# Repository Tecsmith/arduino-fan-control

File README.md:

# Qwiic Fan Control Module

- This is the **EAGLE** *PCB* design project
- For the **Arduino** *code* library please see [Tecsmith](https://github.com/Tecsmith)/[Tecsmith_AMC6821](https://github.com/Tecsmith/Tecsmith_AMC6821)

AMC6821 based Fan Control Module with Qwiic connectors for integration into 3.3V MCU projects.

| &#8505; | URL |
|--------:|-----|
| Project website | [tecsmith.github.io/arduino-fan-control](https://tecsmith.github.io/arduino-fan-control/) |
| Quick link | [`c1k.it/amc6`](http://c1k.it/amc6) |
| Github EAGLE-CAD Source | https://github.com/Tecsmith/arduino-fan-control/tree/master/EAGLE |
| Github PlatformIO Source | https://github.com/Tecsmith/arduino-fan-control/tree/master/PlatformIO |

## About

Thermal control is often arbitrarily implemented in electronics projects – adoption of fans for heat management is often done without consideration for power consumption or acoustic noise.

Leveraging the Texas Instruments AMC6821 chip, this module adds an intelligent temperature monitor and pulse-width modulation (PWM) fan controller to a fan. It is designed for noise-sensitive or power-sensitive applications that require active system cooling. Using a PWM signal, this device simultaneously drives a fan, monitors remote sensor diode temperatures, and measures/controls the fan speed so that it operates with minimal acoustic noise at the lowest possible speed.

This project is an Open Source Hardware (OSH) project and is based on [SparkFun's Qwiic](https://www.sparkfun.com/qwiic) I<sup>2</sup>C connectors and can be integrated into many 3.3V based MCU's.

## AMC6821
### Intelligent temperature monitor and pulse-width modulation fan controller

The AMC6821 is an intelligent temperature monitor and pulse-width modulation (PWM) fan controller. It is designed for noise-sensitive or power-sensitive applications that require active system cooling. Using a low-frequency or a high-frequency PWM signal, this device can simultaneously drive a fan, monitor remote sensor diode temperatures, and measure and control the fan speed so that it operates with minimal acoustic noise at the lowest possible speed.

The AMC6821 has four fan control modes: *Auto Temperature-Fan* mode, *Software-RPM* mode, *Software-DCY* mode, and *Maximum fast-speed calculated control* mode.  Each mode controls the fan speed by changing the duty cycle of a PWM output.

- <u>**Auto Temperature-Fan**</u> mode is an intelligent, closed-loop control that optimizes fan speed according to user-defined parameters. This mode allows the AMC6821 to run as a stand-alone device without CPU intervention; the fan can continue to be controlled (based on temperature measurements) even if the CPU or system locks up.

- <u>**Software-RPM**</u> mode is a second closed-loop control. In this mode, the AMC6821 adjusts the PWM output to maintain a consistent fan speed at a user-specified target value; that is, the device functions as a fan speed regulator. Software-RPM mode can also be used to allow the AMC6821 to operate as a stand-alone device.

- <u>**Software-DCY**</u> mode is the third mode and is open-loop. In Software-DCY mode, the PWM duty cycle is set directly by the value written to the device.

- <u>**Maximum fast-speed calculated control**</u> mode.

The AMC6821 also has a programmable `SMBALERT` output to indicate error conditions and a dedicated `FAN-FAULT` output to indicate fan failure. The `THERM` pin is a fail-safe output for over-temperature conditions that can be used to throttle a CPU clock. Additionally, the `OVR` pin indicates the over-temperature limit as well. All of the alarm thresholds are set through the device registers. The AMC6821 is available in a QSOP-16 package.

## Project Features

- Designed to be an inline series add-on for existing fan implementations.
- Can be powered from 12V and/or 5V power sources. _(Dependant on Fan required operational voltage.)_
- Support most fan types, 5V~ and 12V
  * 4-wire _(Tachometer + PWM)_
  * 3-wire _(Tachometer Sensor)~_
  * 3-wire _(Locked Rotor Sensor)~_
  * 2-wire~
- Can be run as standalone module.
- Can be chained for up to 9 fans, depending on I<sup>2</sup>C addresses set at A0 and A1 pins.
- Both Qwiic and generic I<sup>2</sup>C headers for communication with 3.3V based MCU boards.

> *~ = with add-on MOSFET*

----------
<p align="center" style="color:#069">&#9733;</p>

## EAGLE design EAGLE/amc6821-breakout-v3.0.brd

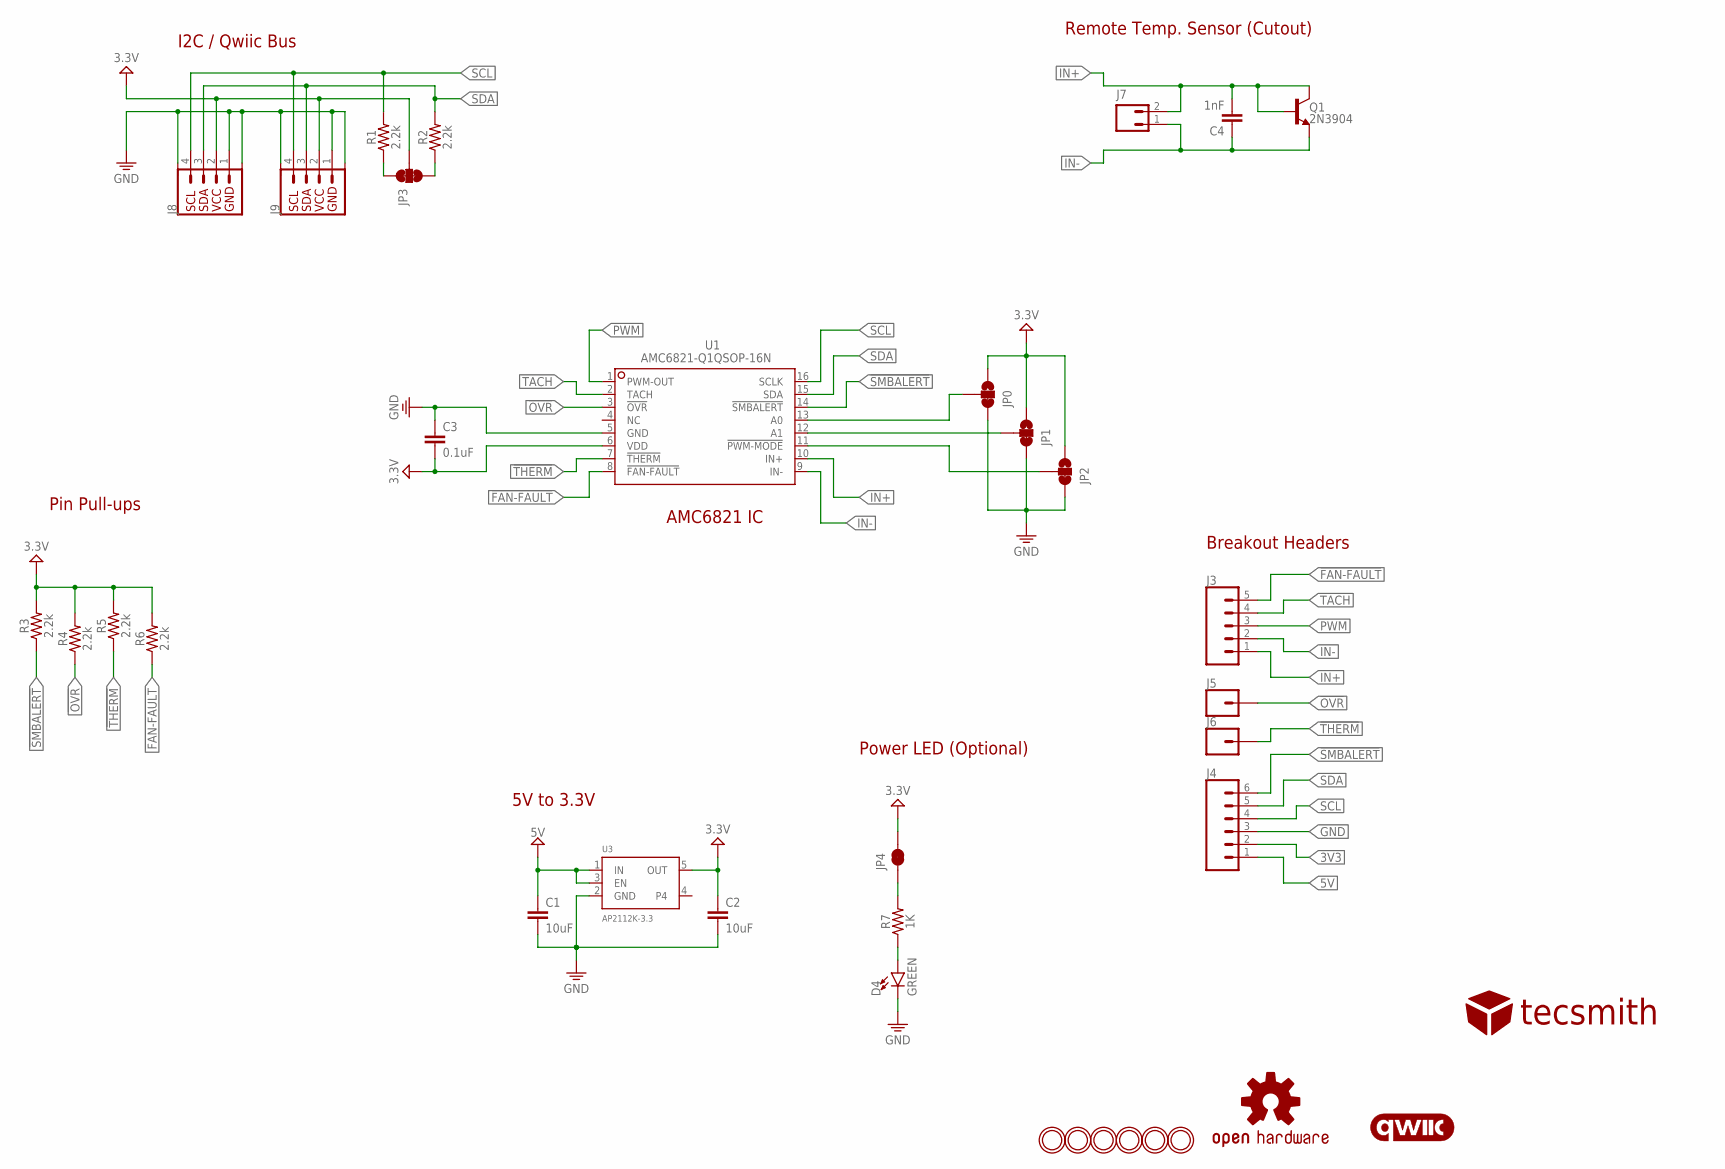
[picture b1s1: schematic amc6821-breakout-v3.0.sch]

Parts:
C1, C2: 10uF; 0603
C3: 0.1uF; 0603
C4: 1nF; 0603
D4: GREEN; LED-0603
J3: CONN_05; 1X05
J4: CONN_06SILK_FEMALE_PTH; 1X06
J5, J6: CONN_01; 1X01
J7: CONN_02; 1X02-LONG
J8, J9: QWIIC_RIGHT_ANGLE; JST04_1MM_RA
JP0, JP1, JP2: JUMPER-SMT_3_1-NC_TRACE_SILK; SMT-JUMPER_3_1-NC_TRACE_SILK
JP3: JUMPER-SMT_3_2-NC_TRACE_SILK; SMT-JUMPER_3_2-NC_TRACE_SILK
JP4: JUMPER-SMT_2_NC_TRACE_SILK; SMT-JUMPER_2_NC_TRACE_SILK
LOGO1: OSHW-LOGOS; OSHW-LOGO-S
LOGO2: QWIIC_LOGO_6MM; QWIIC_6MM
Q1: 2N3904; SOT23-3
R1, R2, R3, R4, R5, R6: 2.2k; 0603
R7: 1K; 0805
U1: AMC6821-Q1QSOP-16N; QSOP-16N
U3: AP2112K-3.3; SOT23-5
U$1: TECSMITH-LOGO
U$4, U$5, U$7, U$8, U$9, U$10: MOUNTINGHOLE2.5; MOUNTINGHOLE_2.5_PLATED

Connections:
3V3: C2.1, C3.2, J4.2, J8.2, J9.2, JP0.1, JP1.1, JP2.1, JP3.2, JP4.2, R3.2, R4.2, R5.2, R6.2, U1.6 (VDD), U3.5 (OUT)
5V: C1.1, J4.1, U3.1 (IN), U3.3 (EN)
!FAN-FAULT: J3.5, R6.1, U1.8 (!FAN-FAULT)
!OVR: J5.1, R4.1, U1.3 (!OVR)
!SMBALERT: J4.6, R3.1, U1.14 (!SMBALERT)
!THERM: J6.1, R5.1, U1.7 (!THERM)
GND: C1.2, C2.2, C3.1, D4.C, J4.3, J8.1, J8.NC1, J8.NC2, J9.1, J9.NC1, J9.NC2, JP0.3, JP1.3, JP2.3, U1.5 (GND), U3.2 (GND)
IN+: C4.2, J3.1, J7.2, Q1.1 (B), Q1.3 (C), U1.10 (IN+)
IN-: C4.1, J3.2, J7.1, Q1.2 (E), U1.9 (IN-)
unnamed: JP0.2, U1.13 (A0)
unnamed: JP3.3, R2.1
unnamed: JP3.1, R1.1
unnamed: JP2.2, U1.11 (!PWM-MODE)
unnamed: JP1.2, U1.12 (A1)
unnamed: D4.A, R7.1
unnamed: JP4.1, R7.2
PWM: J3.3, U1.1 (PWM-OUT)
SCL: J4.4, J8.4, J9.4, R1.2, U1.16 (SCLK)
SDA: J4.5, J8.3, J9.3, R2.2, U1.15 (SDA)
TACH: J3.4, U1.2 (TACH)

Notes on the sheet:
I2C / Qwiic Bus
Breakout Headers
5V to 3.3V
AMC6821 IC
Remote Temp. Sensor (Cutout)
Pin Pull-ups
Power LED (Optional)

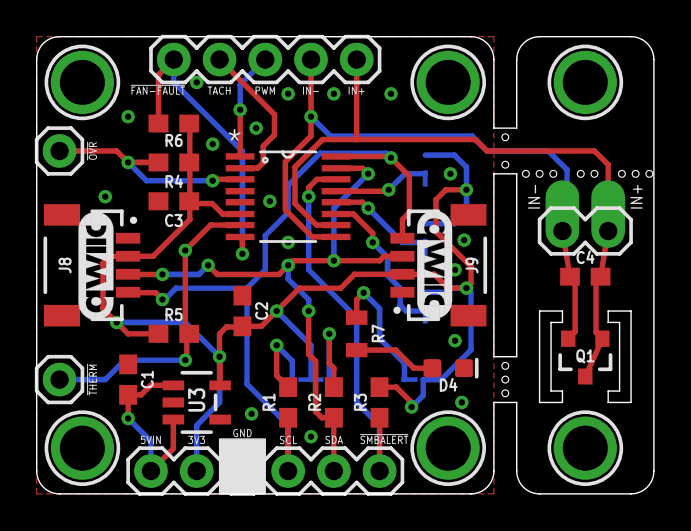
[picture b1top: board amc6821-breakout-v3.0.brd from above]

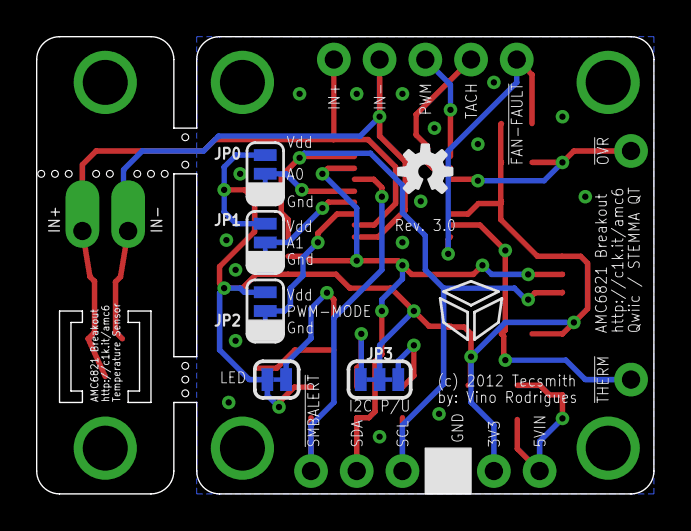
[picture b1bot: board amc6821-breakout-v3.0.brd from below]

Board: 2 copper layers, 34.3 x 25.4 mm, 37 parts (7 on the bottom side), 20 nets.

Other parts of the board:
LOGO3: QWIIC_LOGO_6MM; QWIIC_6MM

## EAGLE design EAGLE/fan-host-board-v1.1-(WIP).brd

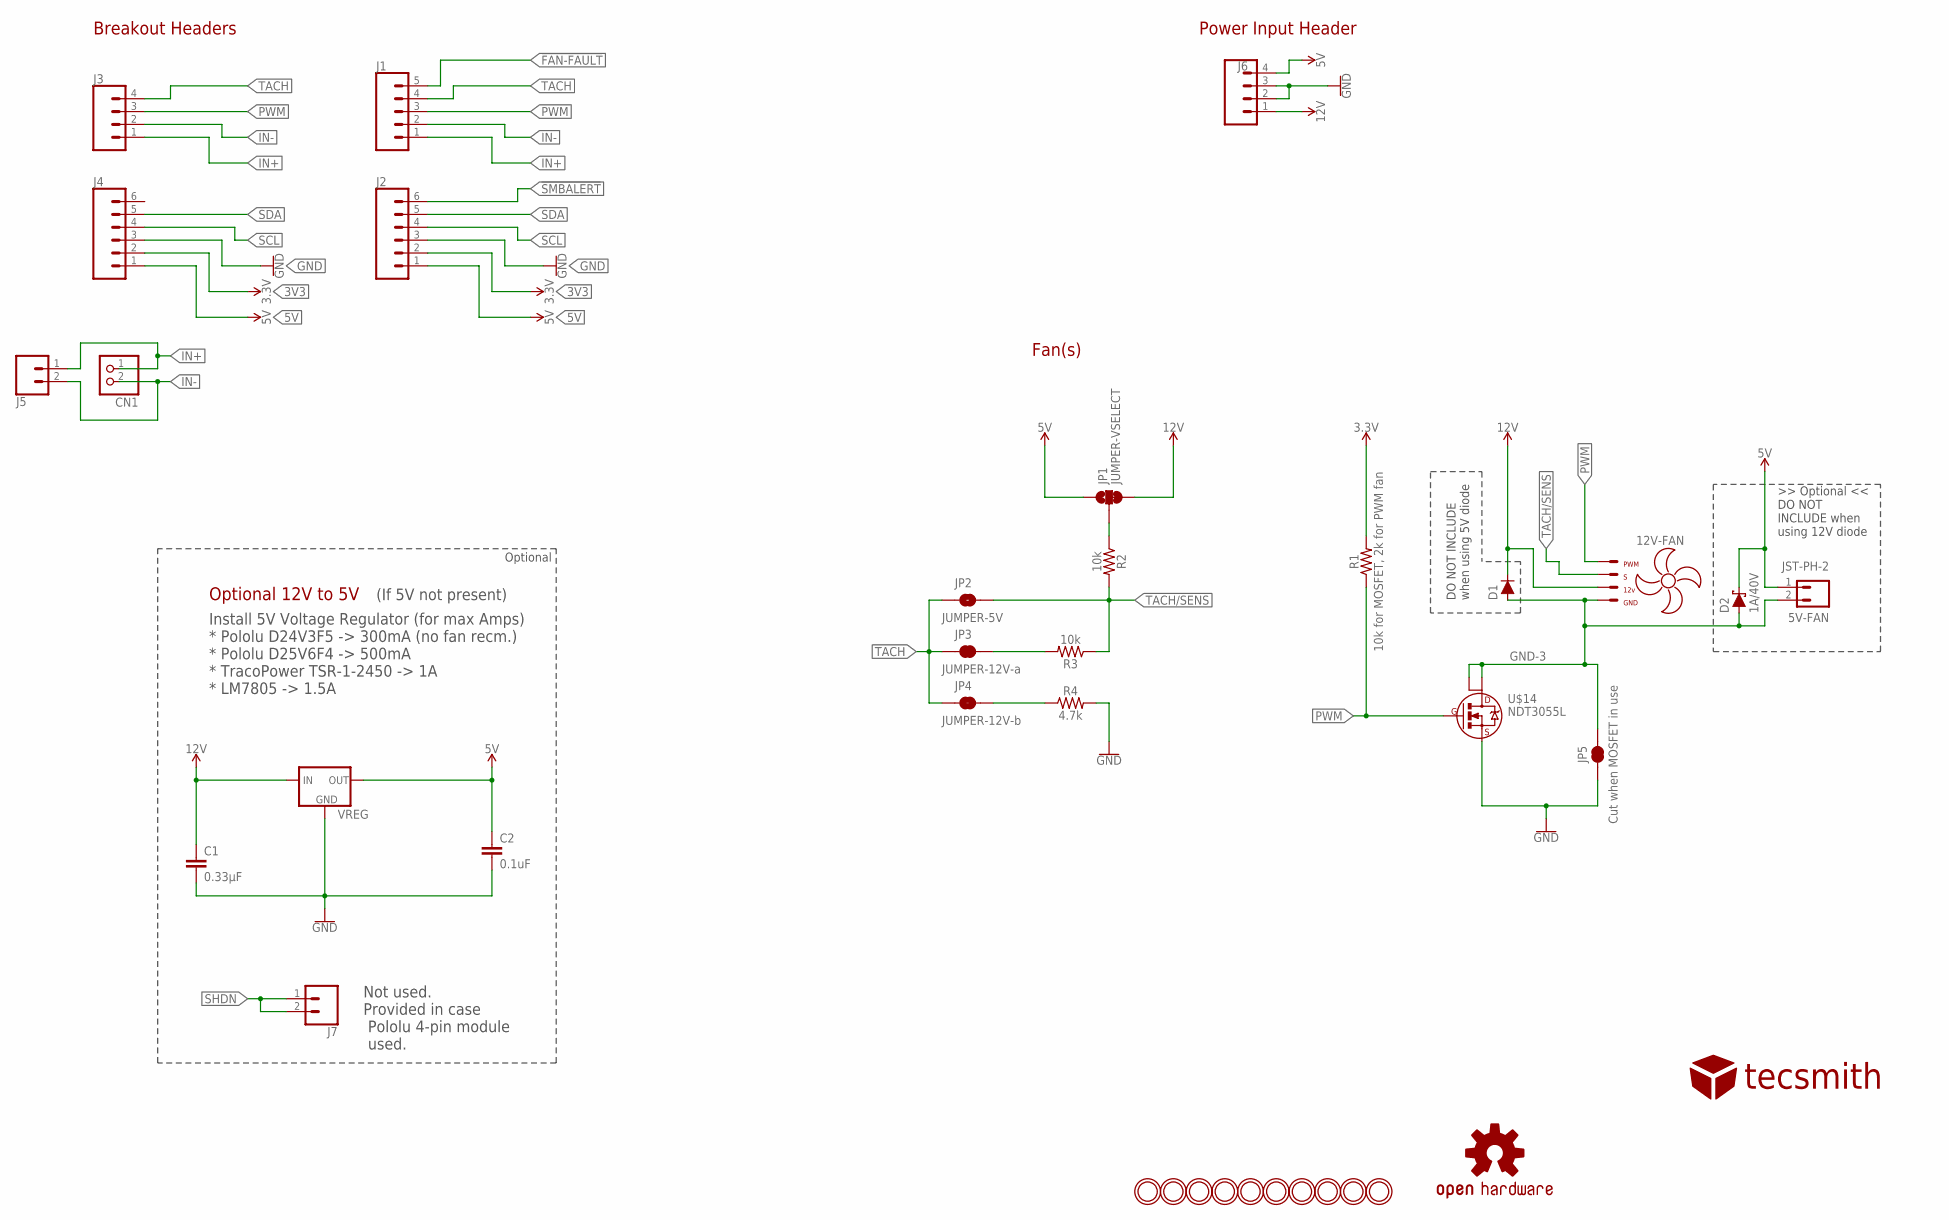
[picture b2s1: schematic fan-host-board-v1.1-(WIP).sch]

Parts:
5V-FAN: JST-PH-2; JST-PH2
12V-FAN: KK-254-4KK-254; MOLEX_47053-1000
C1: 0.33µF; 0805
C2: 0.1uF; 0603
CN1: JST_2PIN-THM; JST-PH-2-THM
D1: 200mA/100V; DIODE-1N4148
D2: 1A/40V; SMA-DIODE
J1: CONN_05; 1X05
J2, J4: CONN_06SILK_FEMALE_PTH; 1X06
J3: CONN_04PTH; 1X04
J5: CONN_02PTH3; 1X02_LONGPADS
J6: CONN_04SCREW; SCREWTERMINAL-3.5MM-4
J7: CONN_021X02_NO_SILK; 1X02_NO_SILK
JP1: JUMPER-VSELECT; SMT-JUMPER_3_1-NC_TRACE_SILK
JP2: JUMPER-5V; SMT-JUMPER_2_NO_SILK
JP3: JUMPER-12V-a; SMT-JUMPER_2_NC_TRACE_SILK
JP4: JUMPER-12V-b; SMT-JUMPER_2_NC_TRACE_SILK
JP5: Cut when MOSFET in use; SMT-JUMPER_2_NC_TRACE_NO-SILK
LOGO1: OSHW-LOGOS; OSHW-LOGO-S
R1: 10k for MOSFET, 2k for PWM fan; 0603
R2, R3: 10k; 0603
R4: 4.7k; 0603
U$1: TECSMITH-LOGO
U$2, U$3, U$4, U$5, U$6, U$7, U$8, U$9, U$10, U$11: MOUNTINGHOLE2.5; MOUNTINGHOLE_2.5_PLATED
U$14: NDT3055L; SOT223
VREG: TRACOPOWER-TSR-1; TRACO-TSR-1

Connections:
3V3: J2.2, J4.2, R1.2
5V: 5V-FAN.1, C2.1, D2.C, J2.1, J4.1, J6.4, JP1.1, VREG.P$+VOUT (OUT)
12V: 12V-FAN.2:+12VDC, C1.1, D1.C, J6.1, JP1.3, VREG.P$+VIN (IN)
!FAN-FAULT: J1.5
!SMBALERT: J2.6
GND: C1.2, C2.2, J2.3, J4.3, J6.2, J6.3, JP5.1, R4.2, U$14.S, VREG.P$GND (GND)
GND-3: 5V-FAN.2, 12V-FAN.1:GND, D1.A, D2.A, JP5.2, U$14.D, U$14.D2
IN+: CN1.1 (2), J1.1, J3.1, J5.1
IN-: CN1.2 (1), J1.2, J3.2, J5.2
unnamed: JP1.2, R2.1
unnamed: JP3.2, R3.2
unnamed: JP4.2, R4.1
PWM: 12V-FAN.4:PWM, J1.3, J3.3, R1.1, U$14.G
SCL: J2.4, J4.4
SDA: J2.5, J4.5
SHDN: J7.1, J7.2
TACH: J1.4, J3.4, JP2.1, JP3.1, JP4.1
TACH/SENS: 12V-FAN.3:TACH, JP2.2, R2.2, R3.1

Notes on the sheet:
Fan(s)
Power Input Header
Optional 12V to 5V
Install 5V Voltage Regulator (for max Amps) * Pololu D24V3F5 -> 300mA (no fan recm.) * Pololu D25V6F4 -> 500mA * TracoPower TSR-1-2450 -> 1A * LM7805 -> 1.5A
Breakout Headers
(If 5V not present)
Optional
Not used. Provided in case Pololu 4-pin module used.
DO NOT INCLUDE when using 5V diode

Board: 2 copper layers, 37 parts (6 on the bottom side), 16 nets, no tracks yet.

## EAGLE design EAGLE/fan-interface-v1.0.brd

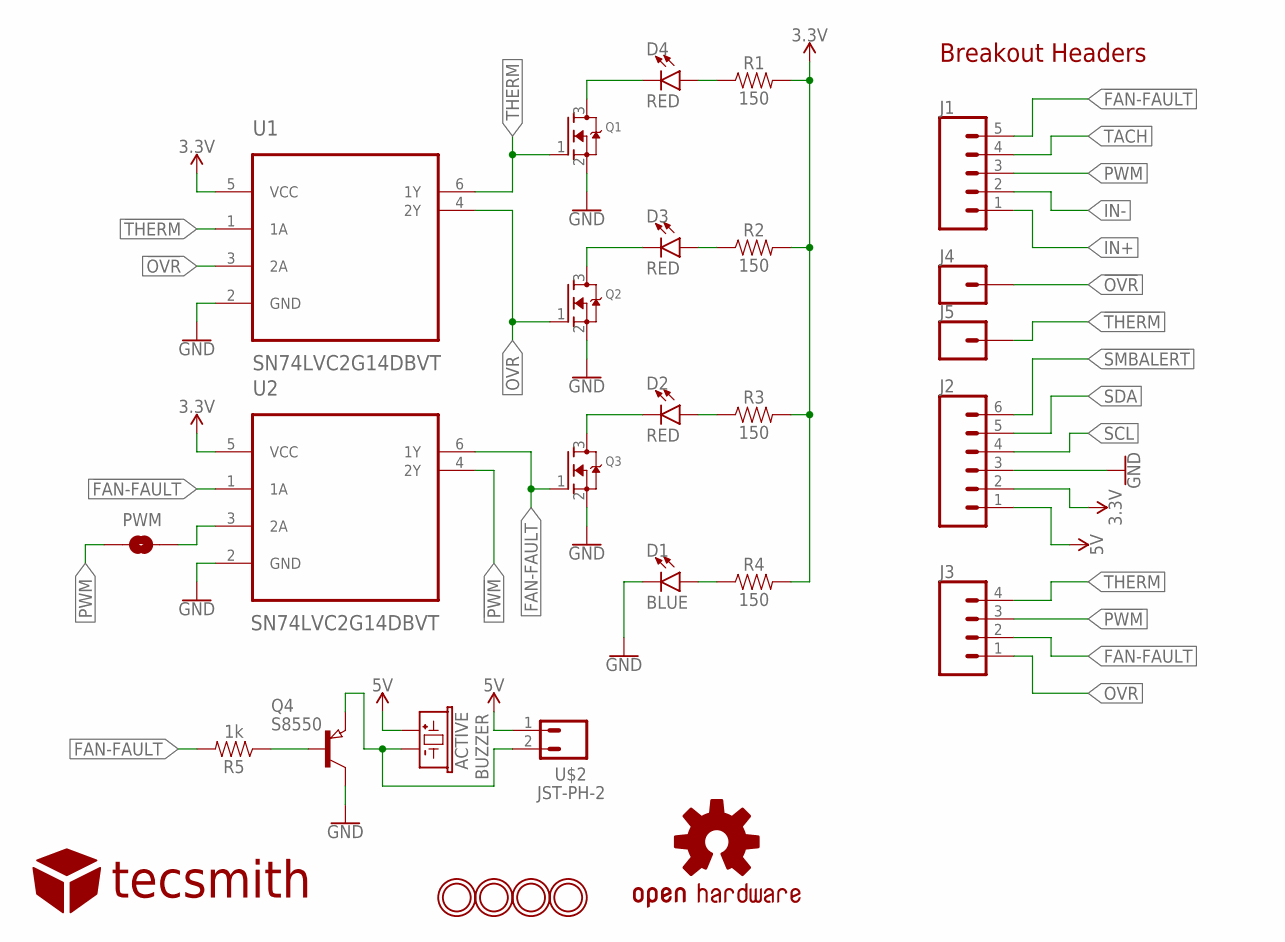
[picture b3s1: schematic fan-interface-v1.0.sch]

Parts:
ACTIVE: BUZZER; BUZZER-SMD
D1: BLUE; LED-0603
D2, D3, D4: RED; LED-0603
J1: CONN_05; 1X05
J2: CONN_06SILK_FEMALE_PTH; 1X06
J3: CONN_04PTH; 1X04
J4, J5: CONN_01; 1X01
LOGO1: OSHW-LOGOS; OSHW-LOGO-S
PWM: JUMPER-SMT_2_NO_SILK; SMT-JUMPER_2_NO_SILK
Q1, Q2, Q3: MOSFET-NREFLOW; SOT23
Q4: S8550; SOT23
R1, R2, R3, R4: 150; 0603
R5: 1k; 0603
U1, U2: SN74LVC2G14DBVT; SOT95P280X145-6N
U$1: TECSMITH-LOGO
U$2: JST-PH-2; JST-PH2
U$7, U$8, U$9, U$10: MOUNTINGHOLE2.5; MOUNTINGHOLE_2.5_PLATED

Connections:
3.3V: J2.2, R1.2, R2.2, R3.2, R4.2, U1.5 (VCC), U2.5 (VCC)
5V: ACTIVE.+ (1), ACTIVE.+1 (1), J2.1, U$2.1
!FAN-FAULT: J1.5, U2.1 (1A)
!OVR: J4.1, U1.3 (2A)
!PWM: J3.3, U2.4 (2Y)
!SMBALERT: J2.6
!THERM: J5.1, U1.1 (1A)
FAN-FAULT: J3.2, Q3.1 (G), R5.2, U2.6 (1Y)
GND: D1.C, J2.3, Q1.2 (S), Q2.2 (S), Q3.2 (S), Q4.3 (C), U1.2 (GND), U2.2 (GND)
IN+: J1.1
IN-: J1.2
unnamed: D4.C, Q1.3 (D)
unnamed: D4.A, R1.1
unnamed: D3.A, R2.1
unnamed: D3.C, Q2.3 (D)
unnamed: PWM.2, U2.3 (2A)
unnamed: Q4.1 (B), R5.1
unnamed: D2.A, R3.1
unnamed: D2.C, Q3.3 (D)
unnamed: D1.A, R4.1
unnamed: ACTIVE.- (2), ACTIVE.-1 (2), Q4.2 (E), U$2.2
OVR: J3.1, Q2.1 (G), U1.4 (2Y)
PWM: J1.3, PWM.1
SCL: J2.4
SDA: J2.5
TACH: J1.4
THERM: J3.4, Q1.1 (G), U1.6 (1Y)

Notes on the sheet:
Breakout Headers

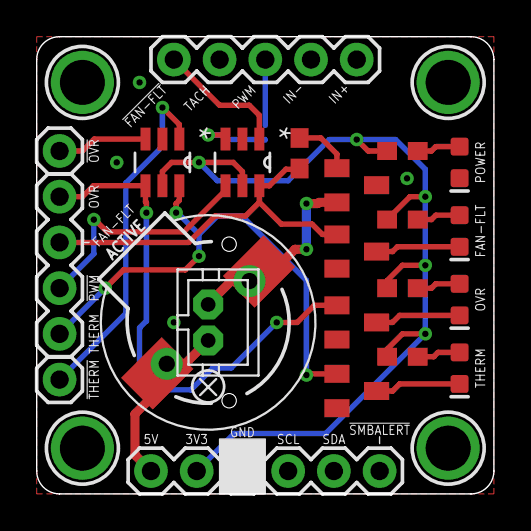
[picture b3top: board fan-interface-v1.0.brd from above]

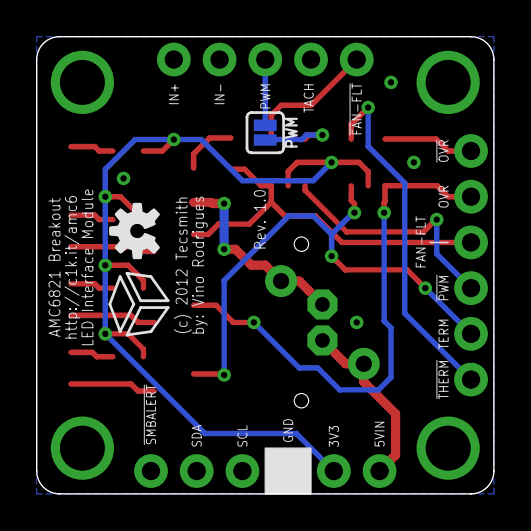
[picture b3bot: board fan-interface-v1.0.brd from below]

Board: 2 copper layers, 25.4 x 25.4 mm, 29 parts (3 on the bottom side), 21 nets.

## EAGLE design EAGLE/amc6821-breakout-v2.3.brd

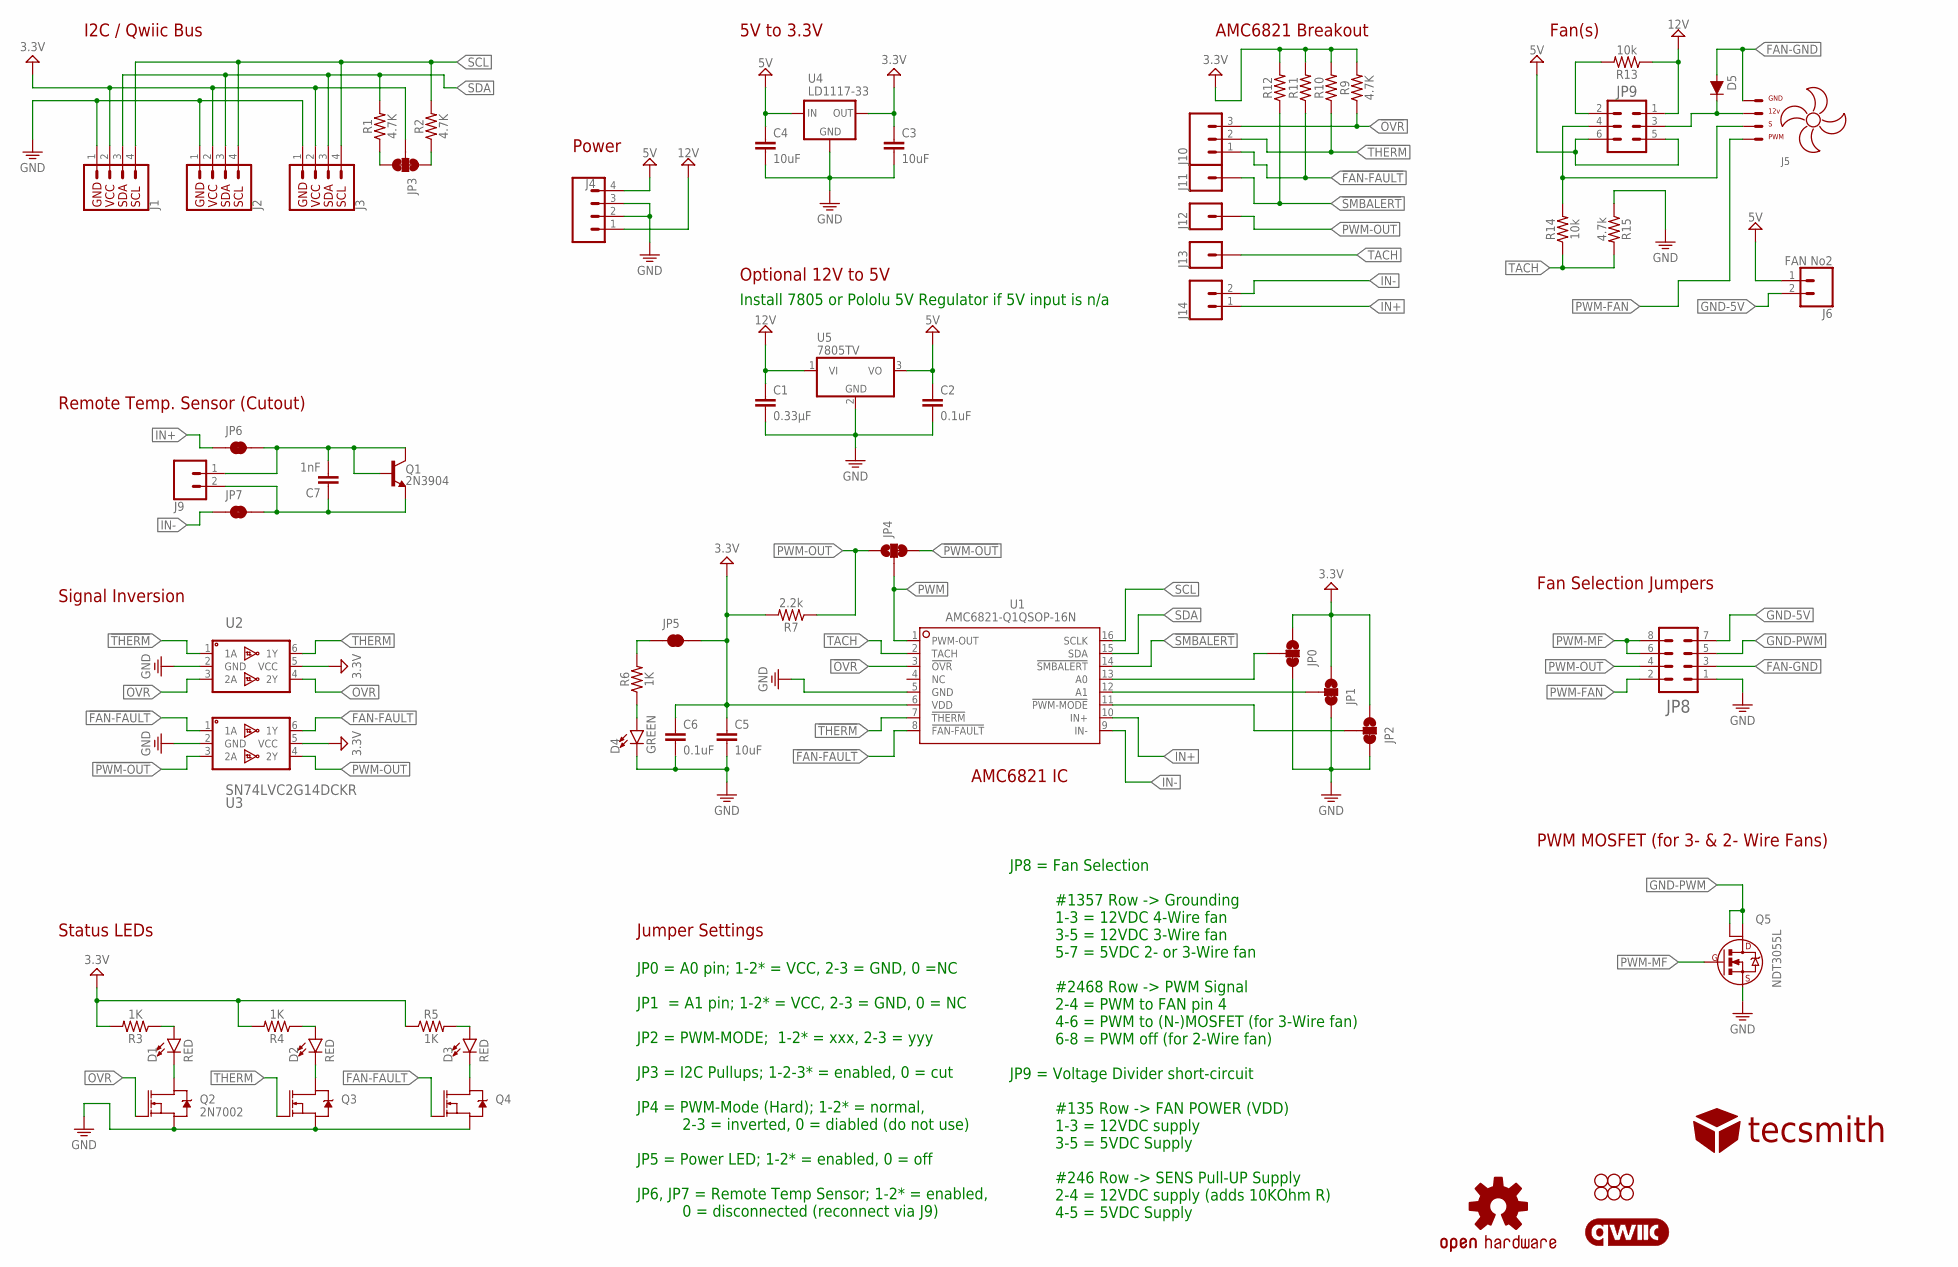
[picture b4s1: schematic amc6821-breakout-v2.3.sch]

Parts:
C1: 0.33µF; 0805
C2, C6: 0.1uF; 0603
C3, C4, C5: 10uF; 0603
C7: 1nF; 0603
D1, D2, D3: RED; LED-0603
D4: GREEN; LED-0603
D5: 200mA/100V/1V; DIODE-1N4148
H1, H2, H3, H4, H5, H6: STAND-OFF
J1, J2: QWIIC_RIGHT_ANGLE; JST04_1MM_RA
J3: I2C_STANDARD; 1X04
J4: CONN_04SCREW; SCREWTERMINAL-3.5MM-4
J5: KK-254-4KK-254; MOLEX_47053-1000
J6: FAN No2; JST-PH2
J9, J14: CONN_02; 1X02
J10: 455-1750-1-ND; 1X03
J11, J12, J13: CONN_01; 1X01
JP0, JP1, JP2, JP4: JUMPER-SMT_3_1-NC_TRACE_SILK; SMT-JUMPER_3_1-NC_TRACE_SILK
JP3: JUMPER-SMT_3_2-NC_TRACE_SILK; SMT-JUMPER_3_2-NC_TRACE_SILK
JP5, JP6, JP7: JUMPER-SMT_2_NC_TRACE_SILK; SMT-JUMPER_2_NC_TRACE_SILK
JP8: CONN_04X2; 2X4
JP9: CONN_03X2NO_SILK; 2X3-NS
LOGO1: OSHW-LOGOS; OSHW-LOGO-S
LOGO2: QWIIC_LOGO_6MM; QWIIC_6MM
Q1: 2N3904; SOT23-3
Q2: 2N7002; SOT23-3
Q3, Q4: 2N7002-BSS138; SOT23-3
Q5: NDT3055L; SOT223
R1, R2, R9, R10, R11, R12: 4.7K; 0805
R3, R4, R5, R6: 1K; 0805
R7: 2.2k; 0603
R13, R14: 10k; 0603
R15: 4.7k; 0603
U1: AMC6821-Q1QSOP-16N; QSOP-16N
U2, U3: SN74LVC2G14DCKR; SOT65P210X110-6N
U4: LD1117-33; SOT223
U5: 7805TV; TO220V
U$1: TECSMITH-LOGO

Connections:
3V3: C3.1, C5.1, C6.1, J1.2, J2.2, J3.2, JP0.1, JP1.1, JP2.1, JP3.2, JP5.2, R3.2, R4.2, R5.1, R7.2, R9.2, R10.2, R11.2, R12.2, U1.6 (VDD), U2.5 (VCC), U3.5 (VCC), U4.2 (OUT)
5V: C2.1, C4.1, J4.4, J6.1, JP9.5, JP9.6, U4.3 (IN), U5.3 (VO)
12V: C1.1, J4.1, JP9.1, R13.1, U5.1 (VI)
!FAN-FAULT: J10.1, R11.1, U1.8 (!FAN-FAULT), U3.1 (1A)
!OVR: J10.3, R9.1, U1.3 (!OVR), U2.3 (2A)
!PWM-OUT: JP4.3, U3.3 (2A)
!SMBALERT: J11.1, R12.1, U1.14 (!SMBALERT)
!THERM: J10.2, R10.1, U1.7 (!THERM), U2.1 (1A)
FAN-FAULT: Q4.1 (G), U3.6 (1Y)
FAN-GND: D5.A, J5.1:GND, JP8.3
GND: C1.2, C2.2, C3.2, C4.2, C5.2, C6.2, D4.C, J1.1, J2.1, J3.1, J4.2, J4.3, JP0.3, JP1.3, JP2.3, JP8.1, Q2.2 (S), Q3.2 (S), Q4.2 (S), Q5.S, R15.1, U1.5 (GND), U2.2 (GND), U3.2 (GND), U4.1 (GND), U5.2 (GND)
GND-5V: J6.2, JP8.7
GND-PWM: JP8.5, Q5.D, Q5.D2
IN+: J14.1, JP6.1, U1.10 (IN+)
IN-: J14.2, JP7.1, U1.9 (IN-)
unnamed: JP0.2, U1.13 (A0)
unnamed: C7.2, J9.1, JP6.2, Q1.1 (B), Q1.3 (C)
unnamed: JP3.3, R1.1
unnamed: JP3.1, R2.1
unnamed: JP2.2, U1.11 (!PWM-MODE)
unnamed: JP1.2, U1.12 (A1)
unnamed: C7.1, J9.2, JP7.2, Q1.2 (E)
unnamed: D4.A, R6.1
unnamed: D3.A, R5.2
unnamed: D3.C, Q4.3 (D)
unnamed: D1.A, R3.1
unnamed: JP5.1, R6.2
unnamed: D1.C, Q2.3 (D)
unnamed: D2.C, Q3.3 (D)
unnamed: D2.A, R4.1
unnamed: J5.3:TACH, JP9.4, R14.2
unnamed: JP9.2, R13.2
OVR: Q2.1 (G), U2.4 (2Y)
PWM: JP4.2, U1.1 (PWM-OUT)
PWM-FAN: J5.4:PWM, JP8.2
PWM-MF: JP8.6, JP8.8, Q5.G
PWM-OUT: J12.1, JP4.1, JP8.4, R7.1, U3.4 (2Y)
SCL: J1.4, J2.4, J3.4, R2.2, U1.16 (SCLK)
SDA: J1.3, J2.3, J3.3, R1.2, U1.15 (SDA)
TACH: J13.1, R14.1, R15.2, U1.2 (TACH)
THERM: Q3.1 (G), U2.6 (1Y)
VDD: D5.C, J5.2:+12VDC, JP9.3

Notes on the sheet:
I2C / Qwiic Bus
Fan(s)
AMC6821 Breakout
Power
Optional 12V to 5V
5V to 3.3V
AMC6821 IC
Remote Temp. Sensor (Cutout)
PWM MOSFET (for 3- & 2- Wire Fans)
Fan Selection Jumpers
Signal Inversion
Status LEDs
JP0 = A0 pin; 1-2* = VCC, 2-3 = GND, 0 =NC JP1 = A1 pin; 1-2* = VCC, 2-3 = GND, 0 = NC JP2 = PWM-MODE; 1-2* = xxx, 2-3 = yyy JP3 = I2C Pullups; 1-2-3* = enabled, 0 = cut JP4 = PWM-Mode (Hard); 1-2* = normal, 2-3 = inverted, 0 = diabled (do not use) JP5 = Power LED; 1-2* = enabled, 0 = off JP6, JP7 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
Jumper Settings
JP8 = Fan Selection #1357 Row -> Grounding 1-3 = 12VDC 4-Wire fan 3-5 = 12VDC 3-Wire fan 5-7 = 5VDC 2- or 3-Wire fan #2468 Row -> PWM Signal 2-4 = PWM to FAN pin 4 4-6 = PWM to (N-)MOSFET (for 3-Wire fan) 6-8 = PWM off (for 2-Wire fan) JP9 = Voltage Divider short-circuit #135 Row -> FAN POWER (VDD)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
Install 7805 or Pololu 5V Regulator if 5V input is n/a

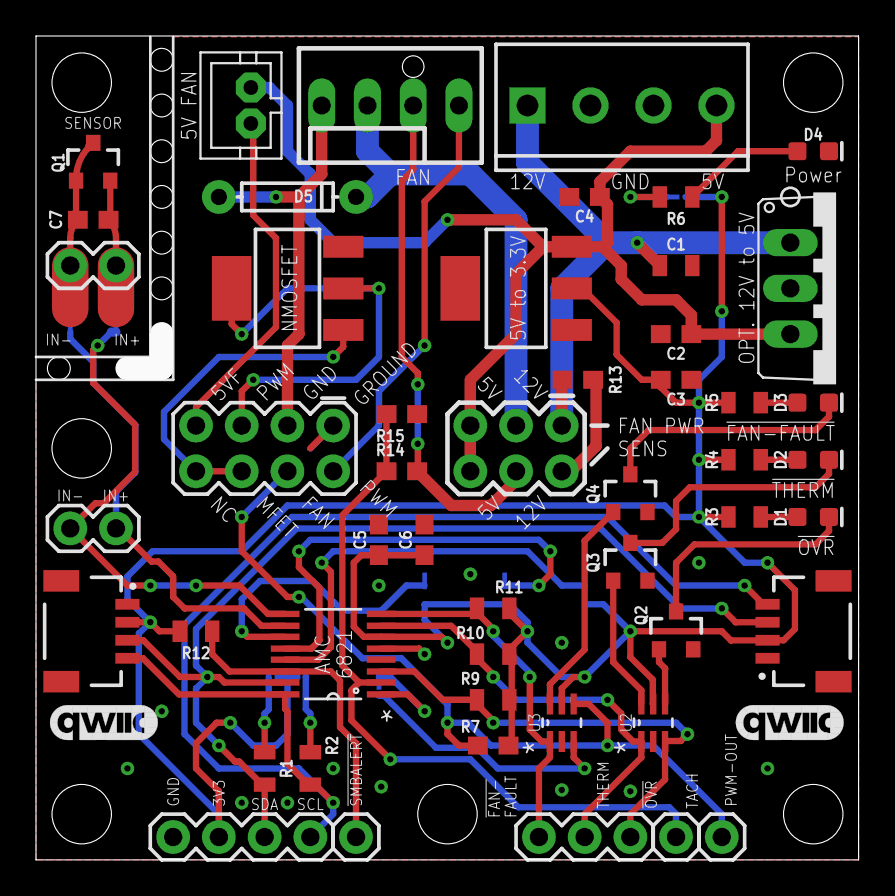
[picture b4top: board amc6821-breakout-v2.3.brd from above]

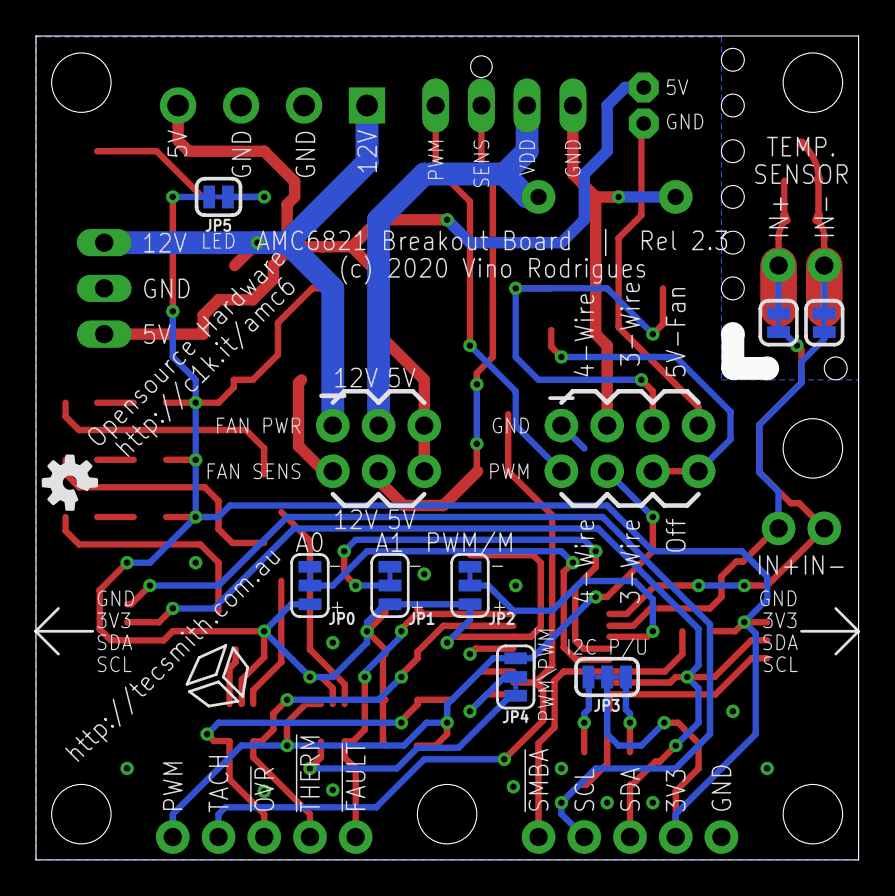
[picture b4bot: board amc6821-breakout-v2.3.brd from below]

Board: 2 copper layers, 44.4 x 44.5 mm, 68 parts (10 on the bottom side), 42 nets.

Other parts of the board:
LOGO3: QWIIC_LOGO_6MM; QWIIC_6MM

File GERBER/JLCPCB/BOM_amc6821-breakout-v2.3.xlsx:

Comment | Designator | Footprint | LCSC Part #（optional） | LCSC Type | Checked | Description
2N7002 N-MOSFET | Q2, Q3, Q4 | SOT-23-3 | C8545 | Basic | ✓ | N-channel MOSFETs
0.33UF (330NF) | C1 | 805 | C1740 | Basic | ✓ | 0.33¬µF/330nF ceramic capacitors
0.1UF (100NF) | C2, C6 | 805 | C49678 | Basic | ✓ | 0.1¬µF ceramic capacitors
10UF | C3, C4, C5 | 805 | C15850 | Basic | ✓ | 10.0¬µF ceramic capacitors
1.0NF (1000PF) | C7 | 805 | C46653 | Basic | ✓ | 1nF/1,000pF ceramic capacitors
4.7KOHM 1/10W-1% | R1, R2, R9, R10, R11, R12, R15 | 805 | C17673 | Basic | ✓ | 4.7k resistor
1KOHM 1/10W-1% | R3, R4, R5, R6 | 805 | C17513 | Basic | ✓ | 1k resistor
2.2KOHM 1/10W-1% | R7 | 805 | C17520 | Basic | ✓ | 2.2k resistor
10KOHM 1/10W-1% | R13, R14 | 805 | C17414 | Basic | ✓ | 10k resistor
LED-RED | D1, D2, D3 | LED_0805 | C84256 | Basic | ✓ | Red SMD LED
LED-GREEN | D4 | LED_0805 | C2297 | Basic | ✓ | Green SMD LED
DIODE-1N4148 | D5 | --- | --- | --- | - | Through hole diode
2N3904 | Q1 | SOT-23-3 | C20526 | Basic | ✓ | 2N3904 NPN transistor
AMC6821-Q1QSOP-16N | U1 | QSOP-16N | C555157 | Extended | 0 | AMC6821
NDT3055L | Q5 | SOT-223-3 | C725128 | Extended | ✓ | N-channel MOSFET for PWM
SN74LVC2G14DCKR | U2, U3 | SOT-363 | C37361 | Extended | ✓ | DUAL SCHMITT-TRIGGER INVERTER
AMS1117-3.3 | U4 | SOT-223 | C6186 | Basic | ✓ | LD1117VXX voltage regulator 3.3V
7805TV | U5 | TO220V | --- | --- | - | Positive VOLTAGE REGULATOR

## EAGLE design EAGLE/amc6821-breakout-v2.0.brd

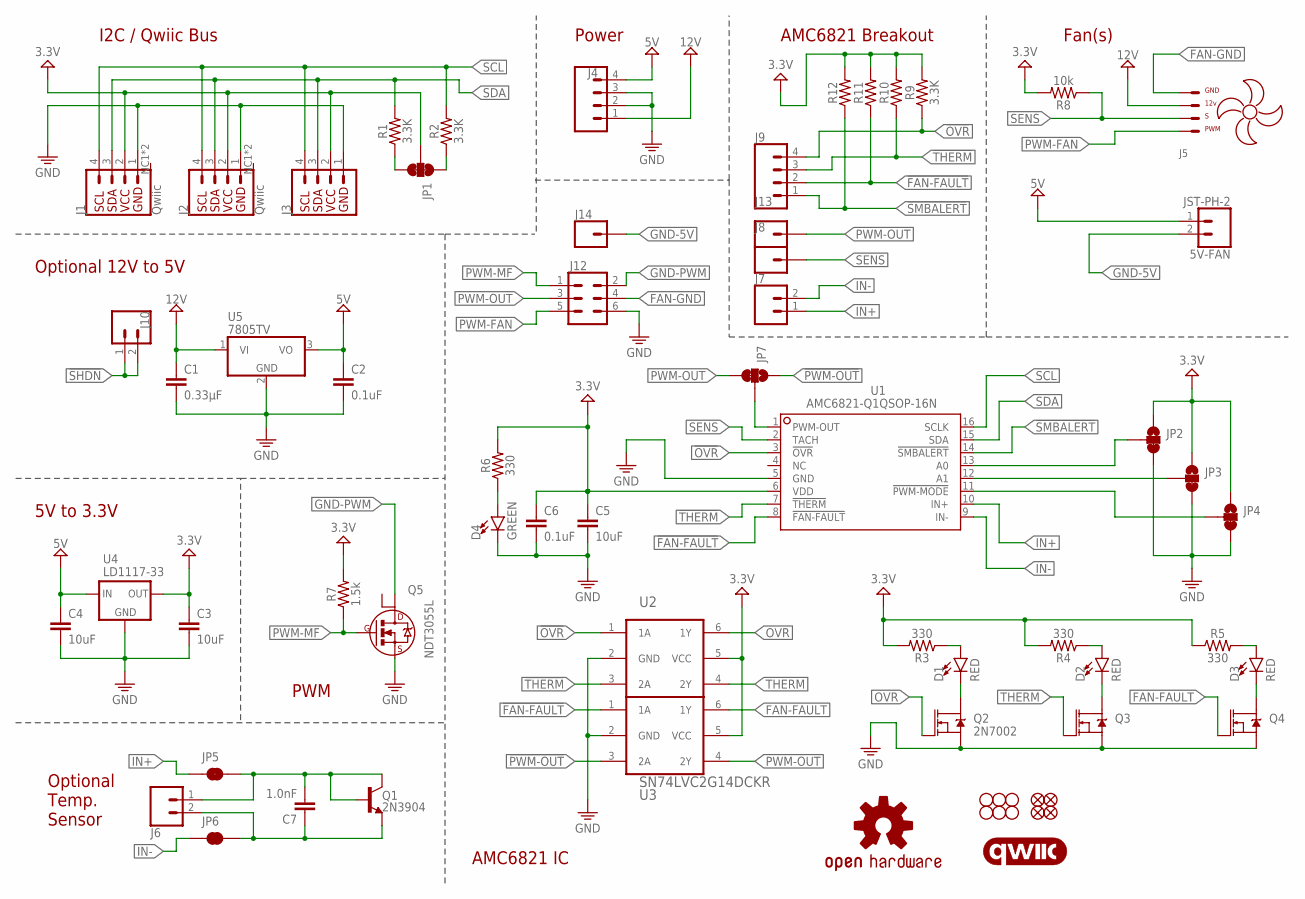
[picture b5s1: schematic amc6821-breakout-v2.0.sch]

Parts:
5V-FAN: JST-PH-2; JST-PH2
C1: 0.33µF; 0805
C2, C6: 0.1uF; 0603
C3, C4, C5: 10uF; 0603
C7: 1.0nF; 0402-TIGHT
D1, D2, D3: RED; LED-0603
D4: GREEN; LED-0603
FD1, FD2, FD3, FD4: FIDUCIALUFIDUCIAL; FIDUCIAL-MICRO
H1, H2, H3, H4, H5, H6: STAND-OFF
J1, J2: Qwiic; JST04_1MM_VERT
J3: I2C_STANDARD; 1X04
J4: CONN_04SCREW; SCREWTERMINAL-3.5MM-4
J5: KK-254-4KK-254; MOLEX_47053-1000
J6, J7: CONN_02; 1X02
J8, J13, J14: CONN_01; 1X01
J9: CONN_04PTH; 1X04
J10: CONN_021X02_NO_SILK; 1X02_NO_SILK
J12: CONN_03X2NO_SILK; 2X3-NS
JP1: JUMPER-SMT_3_2-NC_TRACE_SILK; SMT-JUMPER_3_2-NC_TRACE_SILK
JP2, JP3, JP4, JP7: JUMPER-SMT_3_1-NC_TRACE_SILK; SMT-JUMPER_3_1-NC_TRACE_SILK
JP5, JP6: JUMPER-SMT_2_NC_TRACE_SILK; SMT-JUMPER_2_NC_TRACE_SILK
LOGO1: OSHW-LOGOS; OSHW-LOGO-S
LOGO2: QWIIC_LOGO_6MM; QWIIC_6MM
Q1: 2N3904; SOT23-3
Q2: 2N7002; SOT323
Q3, Q4: 310mA/60V/1.6Ω; SOT323
Q5: NDT3055L; SOT223
R1, R2, R9, R10, R11, R12: 3.3K; 0805
R3, R4, R5, R6: 330; 0805
R7: 1.5k; 0603
R8: 10k; 0603
U1: AMC6821-Q1QSOP-16N; QSOP-16N
U2, U3: SN74LVC2G14DCKR; SOT65P210X110-6N
U4: LD1117-33; SOT223
U5: 7805TV; TO220V

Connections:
3V3: C3.1, C5.1, C6.1, J1.2, J2.2, J3.2, JP1.2, JP2.1, JP3.1, JP4.1, R3.2, R4.2, R5.1, R6.2, R7.2, R8.2, R9.2, R10.2, R11.2, R12.2, U1.6 (VDD), U2.5 (VCC), U3.5 (VCC), U4.2 (OUT)
5V: 5V-FAN.1, C2.1, C4.1, J4.4, U4.3 (IN), U5.3 (VO)
12V: C1.1, J4.1, J5.2:+12VDC, U5.1 (VI)
!FAN-FAULT: J9.2, R11.1, U1.8 (!FAN-FAULT), U3.1 (1A)
!OVR: J9.4, R9.1, U1.3 (!OVR), U2.1 (1A)
!PWM-OUT: JP7.1, U3.3 (2A)
!SHDN: J10.1, J10.2
!SMBALERT: J9.1, R12.1, U1.14 (!SMBALERT)
!THERM: J9.3, R10.1, U1.7 (!THERM), U2.3 (2A)
FAN-FAULT: Q4.1 (G), U3.6 (1Y)
FAN-GND: J5.1:GND, J12.4
GND: C1.2, C2.2, C3.2, C4.2, C5.2, C6.2, D4.C, J1.1, J2.1, J3.1, J4.2, J4.3, J12.6, JP2.3, JP3.3, JP4.3, Q2.2 (S), Q3.2 (S), Q4.2 (S), Q5.S, U1.5 (GND), U2.2 (GND), U3.2 (GND), U4.1 (GND), U5.2 (GND)
GND-5V: 5V-FAN.2, J14.1
GND-PWM: J12.2, Q5.D
IN+: J7.1, JP5.1, U1.10 (IN+)
IN-: J7.2, JP6.1, U1.9 (IN-)
unnamed: JP2.2, U1.13 (A0)
unnamed: C7.2, J6.1, JP5.2, Q1.1 (B), Q1.3 (C)
unnamed: JP1.3, R1.1
unnamed: JP1.1, R2.1
unnamed: JP4.2, U1.11 (!PWM-MODE)
unnamed: JP3.2, U1.12 (A1)
unnamed: C7.1, J6.2, JP6.2, Q1.2 (E)
unnamed: D4.A, R6.1
unnamed: D3.A, R5.2
unnamed: D3.C, Q4.3 (D)
unnamed: D1.A, R3.1
unnamed: D1.C, Q2.3 (D)
unnamed: D2.C, Q3.3 (D)
unnamed: D2.A, R4.1
unnamed: JP7.2, U1.1 (PWM-OUT)
OVR: Q2.1 (G), U2.6 (1Y)
PWM-FAN: J5.4:PWM, J12.5
PWM-MF: J12.1, Q5.G, R7.1
PWM-OUT: J12.3, J13.1, JP7.3, U3.4 (2Y)
SCL: J1.4, J2.4, J3.4, R2.2, U1.16 (SCLK)
SDA: J1.3, J2.3, J3.3, R1.2, U1.15 (SDA)
SENS: J5.3:TACH, J8.1, R8.1, U1.2 (TACH)
THERM: Q3.1 (G), U2.4 (2Y)

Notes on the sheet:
I2C / Qwiic Bus
Fan(s)
AMC6821 Breakout
Power
Optional 12V to 5V
5V to 3.3V
AMC6821 IC
Optional Temp. Sensor
PWM

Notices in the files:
EAGLE/amc6821-breakout-v2.0.brd:
(c) 2020 Vino Rodrigues
EAGLE/amc6821-breakout-v3.0.brd:
(c) 2012 Tecsmith
EAGLE/fan-host-board-v1.1-(WIP).brd:
(c) 2021 Tecsmith / Vino Rodrigues
parts and their libraries:
SparkFun-Connectors: Licensing: Creative Commons ShareAlike 4.0 International - https://creativecommons.org/licenses/by-sa/4.0
microbuilder: This work is placed in the public domain, and may be freely used for commercial and non-commercial work with the following conditions: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
